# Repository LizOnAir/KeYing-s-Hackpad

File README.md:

# Hackpad

This hackpad is a 12 key macropad with a rotary encoder, an OLED Display. It also has 12 SK6812 MINI-E LEDs, and uses KMK firmware.

## Features:
- Upper black layer with transparent bottom acrylic case
- 128x32 OLED Display
- EC11 Rotary encoder
- 12 SK6812 MINI-E LEDs (to produce underglow effect)
- 12 Keys

## CAD Model:
The black upper case and transparent bottom case fits together with 4 M3x5mx4mm heatset inserts and 4 M3x16mm screws.
It has 3 separate printed pieces. The base where the PCB sits, the top cover and also a case for the rotary encoder.

Made in Fusion360.Liz

## PCB
Here's my PCB! It was made in KiCad. 
Schematic

PCB

I used MX_V2 for the keyswitch footprints.
The unicorn silkscreen image was imported from [FLATICON](https://www.flaticon.com/).

## Firmware Overview
This hackpad uses KMK firmware.

- the rotary encoder changes volume and able to act as mousewheel to scroll
- The 12 keys currently act as number pad and arrows key (I'm gonna modify the macros soon to suit my needs)
- The OLED display layers (maybe some cute gif in the future?)

I'm definitely gonna edit the features soon ahhaha

## BOM:
Here should be [everything](https://docs.google.com/spreadsheets/d/1zaCOEk-ZGnszMIk4FFVV_LndeX-SJLxj8WLiJESGuGM/edit?gid=0#gid=0) you need to make this hackpad

- 12x Cherry MX Switches
- 12x DSA Keycaps
- 13x 1N4148 DO-35 Diodes.
- 12x SK6812 MINI-E LEDs
- 1x 0.91" 128x32 OLED Display
- 1x EC11 Rotary Encoder
- 1x XIAO RP2040
- 1x Case (3 printed parts）

## PS
It was my very first time from designing PCB in kicad to modelling in Fusion 360 and also doing firmware stuff.
Although it took longer time than I expected but I still have enthusiasm and hope to be doing more in the future!

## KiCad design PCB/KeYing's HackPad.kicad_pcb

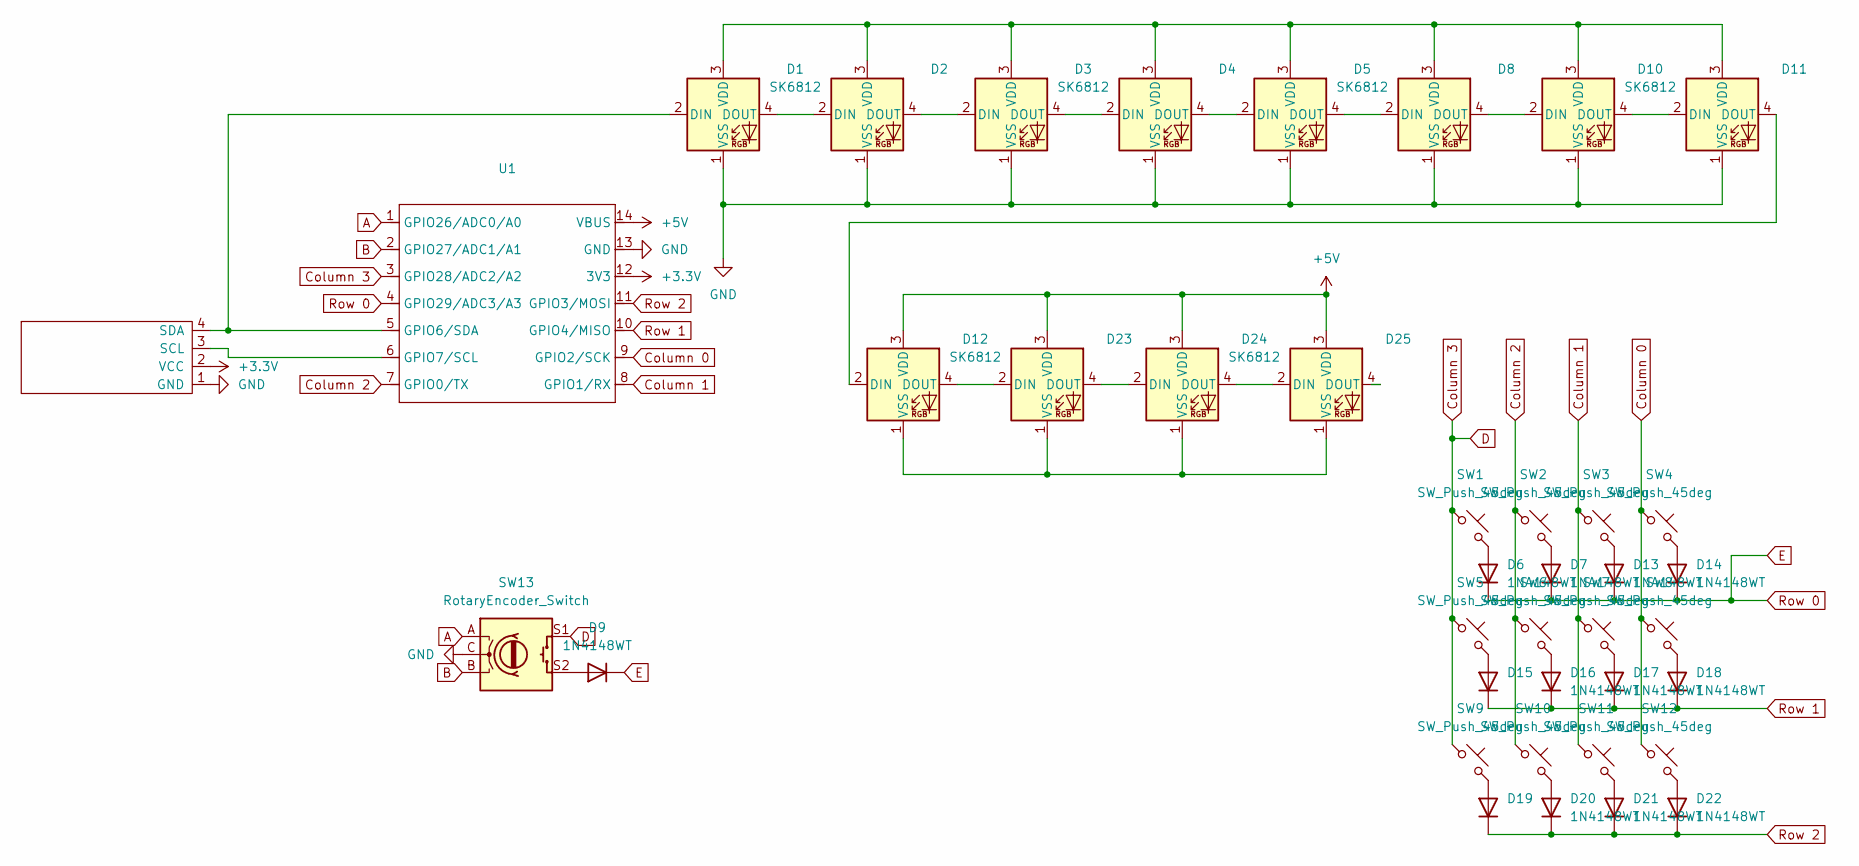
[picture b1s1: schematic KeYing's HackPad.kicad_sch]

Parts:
D1, D2, D3, D4, D5, D8, D10, D11, D12, D23, D24, D25: SK6812; LEDSK6812 MODEL
D6, D7, D9, D13, D14, D15, D16, D17, D18, D19, D20, D21, D22: 1N4148WT; D_SOD-123
SW1, SW2, SW3, SW4, SW5, SW6, SW7, SW8, SW9, SW10, SW11, SW12: SW_Push_45deg; MX CHERRY SWITCH
SW13: RotaryEncoder_Switch; RotaryEncoder_Alps_EC11E-Switch_Vertical_H20mm
U1: XIAO-RP2040-DIP
U2: SSD1306; SSD1306-0.91-OLED-4pin-128x32

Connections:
+3.3V: U1.12 (3V3), U2.2 (VCC)
+5V: D12.3 (VDD), D23.3 (VDD), D24.3 (VDD), D25.3 (VDD), U1.14 (VBUS)
A: SW13.A, U1.1 (GPIO26/ADC0/A0)
B: SW13.B, U1.2 (GPIO27/ADC1/A1)
Column 0: SW4.1, SW8.1, SW12.1, U1.9 (GPIO2/SCK)
Column 1: SW3.1, SW7.1, SW11.1, U1.8 (GPIO1/RX)
Column 2: SW2.1, SW6.1, SW10.1, U1.7 (GPIO0/TX)
Column 3: SW1.1, SW5.1, SW9.1, SW13.S1, U1.3 (GPIO28/ADC2/A2)
E: D6.1 (K), D7.1 (K), D9.1 (K), D13.1 (K), D14.1 (K), U1.4 (GPIO29/ADC3/A3)
GND: D1.1 (VSS), D2.1 (VSS), D3.1 (VSS), D4.1 (VSS), D5.1 (VSS), D8.1 (VSS), D10.1 (VSS), D11.1 (VSS), SW13.C, U1.13 (GND), U2.1 (GND)
unnamed: D1.2 (DIN), U1.5 (GPIO6/SDA), U2.4 (SDA)
unnamed: D1.4 (DOUT), D2.2 (DIN)
unnamed: D1.3 (VDD), D2.3 (VDD), D3.3 (VDD), D4.3 (VDD), D5.3 (VDD), D8.3 (VDD), D10.3 (VDD), D11.3 (VDD)
unnamed: D2.4 (DOUT), D3.2 (DIN)
unnamed: D3.4 (DOUT), D4.2 (DIN)
unnamed: D4.4 (DOUT), D5.2 (DIN)
unnamed: D5.4 (DOUT), D8.2 (DIN)
unnamed: D6.2 (A), SW1.2
unnamed: D7.2 (A), SW2.2
unnamed: D9.2 (A), SW13.S2
unnamed: D8.4 (DOUT), D10.2 (DIN)
unnamed: D10.4 (DOUT), D11.2 (DIN)
unnamed: D11.4 (DOUT), D12.2 (DIN)
unnamed: D12.4 (DOUT), D23.2 (DIN)
unnamed: D12.1 (VSS), D23.1 (VSS), D24.1 (VSS), D25.1 (VSS)
unnamed: D13.2 (A), SW3.2
unnamed: D14.2 (A), SW4.2
unnamed: D15.2 (A), SW5.2
unnamed: D16.2 (A), SW6.2
unnamed: D17.2 (A), SW7.2
unnamed: D18.2 (A), SW8.2
unnamed: D19.2 (A), SW9.2
unnamed: D20.2 (A), SW10.2
unnamed: D21.2 (A), SW11.2
unnamed: D22.2 (A), SW12.2
unnamed: D23.4 (DOUT), D24.2 (DIN)
unnamed: D24.4 (DOUT), D25.2 (DIN)
unnamed: U1.6 (GPIO7/SCL), U2.3 (SCL)
Row 1: D15.1 (K), D16.1 (K), D17.1 (K), D18.1 (K), U1.10 (GPIO4/MISO)
Row 2: D19.1 (K), D20.1 (K), D21.1 (K), D22.1 (K), U1.11 (GPIO3/MOSI)

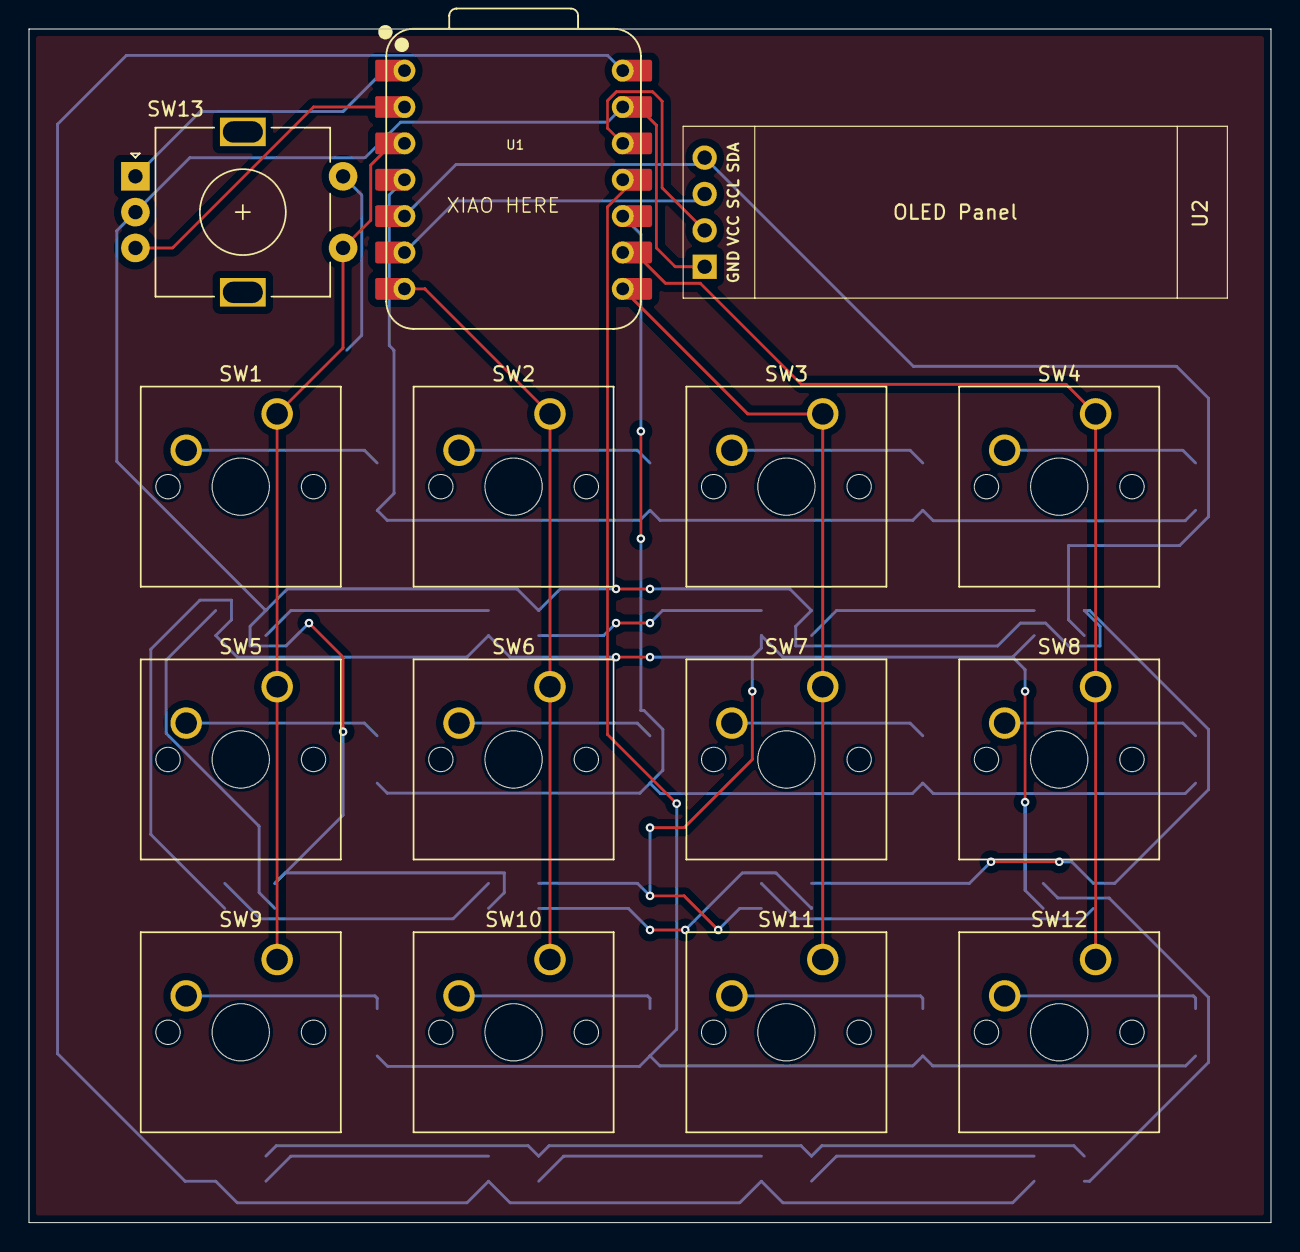
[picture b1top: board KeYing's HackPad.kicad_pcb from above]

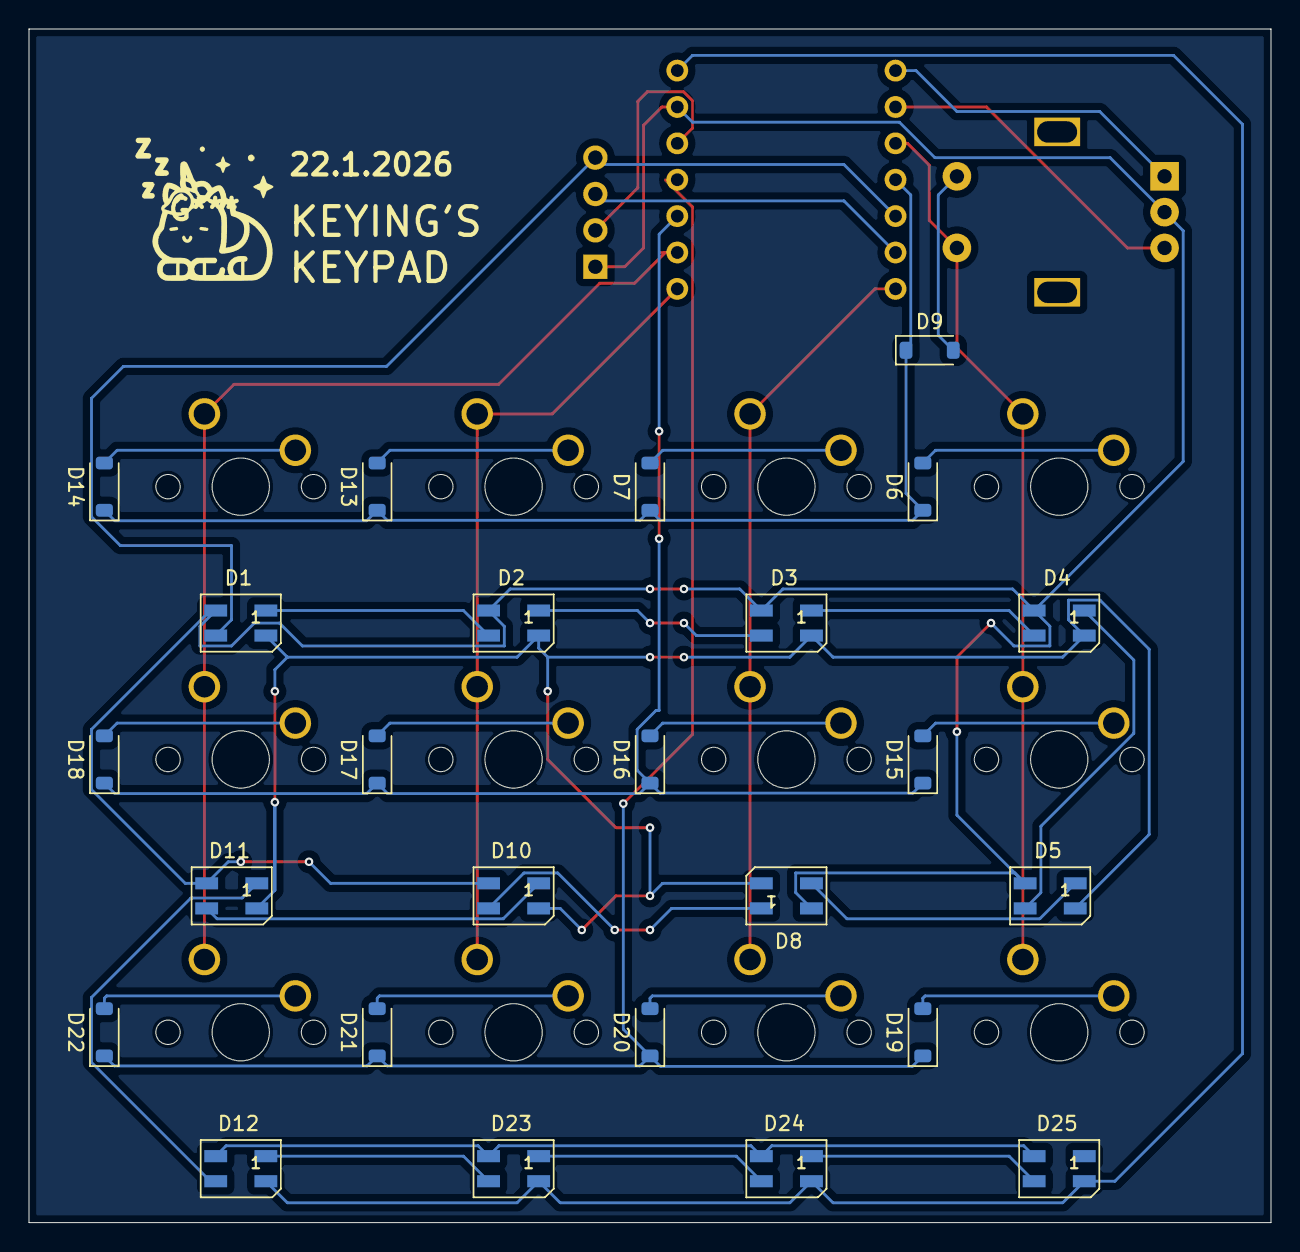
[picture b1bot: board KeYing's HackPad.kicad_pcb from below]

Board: 2 copper layers, 86.7 x 83.3 mm, 40 parts (25 on the bottom side), 40 nets.

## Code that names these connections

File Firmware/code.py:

print("Starting")

import board

from kmk.kmk_keyboard import KMKKeyboard
from kmk.keys import KC
from kmk.scanners import DiodeOrientation
from kmk.modules.encoder import EncoderHandler
from kmk.extensions.media_keys import MediaKeys
from kmk.modules.mouse_keys import MouseKeys

keyboard = KMKKeyboard()

keyboard.col_pins = (board.GPIO2, board.GPIO1, board.GPIO0, board.GPIO28)
keyboard.row_pins = (board.GPIO0, board.GPIO4, board.GPIO3,)
keyboard.diode_orientation = DiodeOrientation.COL2ROW

encoder = EncoderHandler()
keyboard.modules.append(encoder)
keyboard.modules.append(MediaKeys)
keyboard.modules.append(MouseKeys)

encoder.pins = ((board.GPIO26, board.GPIO27, None),)
RAISE = KC.LT(1,KC.ESC)
TRANS = KC.TRANS

keyboard.keymap = [
                    [RAISE,
                    KC.LSHIFT,  KC.N1, KC.N2, KC.N3,
                    KC.KP_ENTER, KC.N4,  KC.N5,  KC.N6,
                    KC.TAB,  KC.N7,  KC.N8,  KC.N9
                  ],
                [
                    [TRANS,
                    KC.MUTE,  KC.MRWD, KC.MPLY, KC.MFFD,
                    KC.KP_ENTER, KC.N4,  KC.N5,  KC.N6,
                    KC.TAB,  KC.N7,  KC.N8,  KC.N9
                  ],
]
encoder.keymap = [
                    ((KC.VOLD, KC.VOLU),),
                    ((KC.MW_DN,KC.MW_UP),),

]

if __name__ == '__main__':
    keyboard.go()

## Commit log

2026-01-26 Create PCB
2026-01-26 Create e
2026-01-27 Added firmware
2026-01-28 Updated code
2026-01-29 Deleted
2026-01-31 Updated CAD
2026-02-01 Update LED description in README
    Clarified the description of the SK6812 MINI-E LEDs to specify their purpose.
2026-02-01 Added CAD
2026-03-12 Added BOM
